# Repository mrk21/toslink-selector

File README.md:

toslink-selector
================

This device is for switching TOSLINK signals automatically.

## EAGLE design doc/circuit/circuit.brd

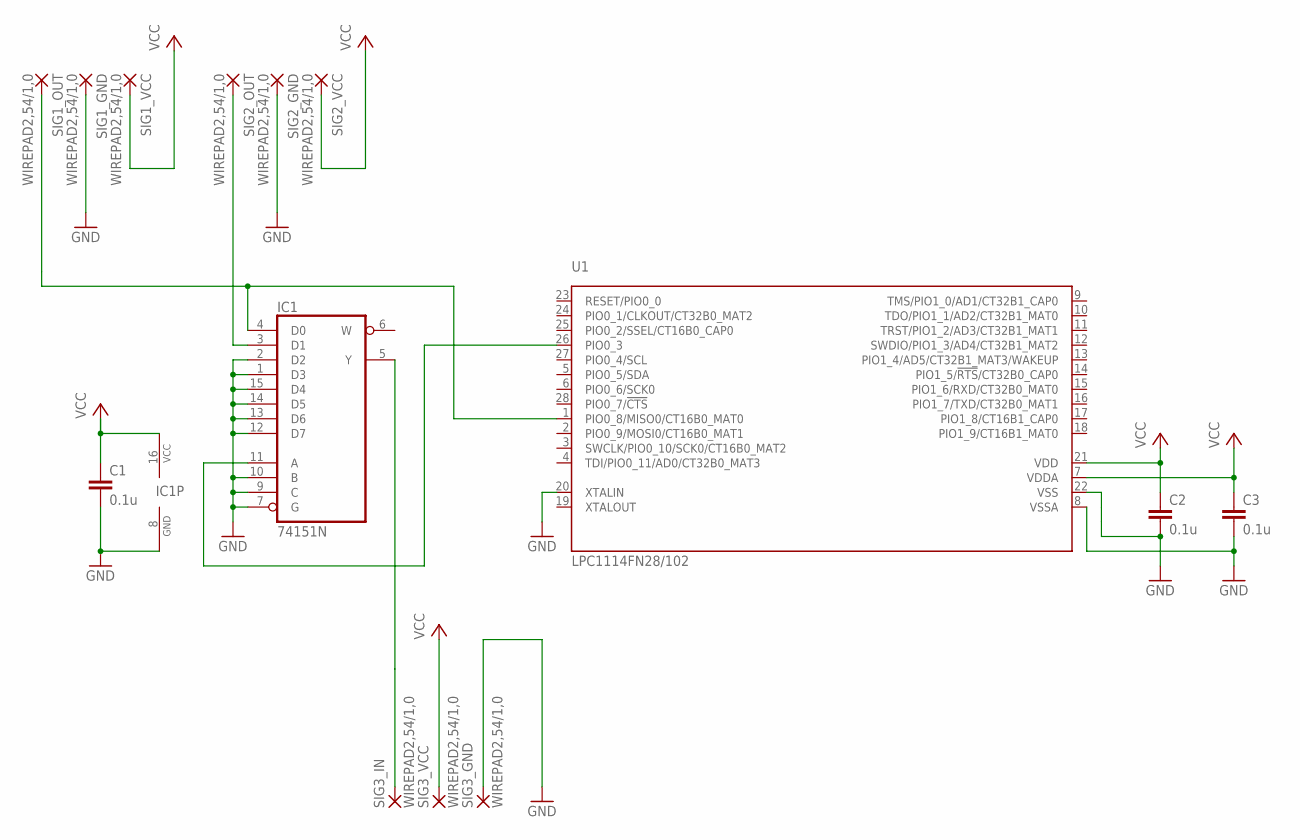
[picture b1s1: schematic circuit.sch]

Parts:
C1, C2, C3: 0.1u; C025-024X044
IC1: 74151N; DIL16
SIG1_GND, SIG1_OUT, SIG1_VCC, SIG2_GND, SIG2_OUT, SIG2_VCC, SIG3_GND, SIG3_IN, SIG3_VCC: WIREPAD2,54/1,0; 2,54/1,0
U1: LPC1114FN28/102; SOT117

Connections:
GND: C1.2, C2.2, C3.2, IC1.1 (D3), IC1.2 (D2), IC1.7 (G), IC1.8 (GND), IC1.9 (C), IC1.10 (B), IC1.12 (D7), IC1.13 (D6), IC1.14 (D5), IC1.15 (D4), SIG1_GND.1, SIG2_GND.1, SIG3_GND.1, U1.8 (VSSA), U1.20 (XTALIN), U1.22 (VSS)
unnamed: IC1.4 (D0), SIG1_OUT.1, U1.1 (PIO0_8/MISO0/CT16B0_MAT0)
unnamed: IC1.11 (A), U1.26 (PIO0_3)
unnamed: IC1.5 (Y), SIG3_IN.1
unnamed: IC1.3 (D1), SIG2_OUT.1
VCC: C1.1, C2.1, C3.1, IC1.16 (VCC), SIG1_VCC.1, SIG2_VCC.1, SIG3_VCC.1, U1.7 (VDDA), U1.21 (VDD)

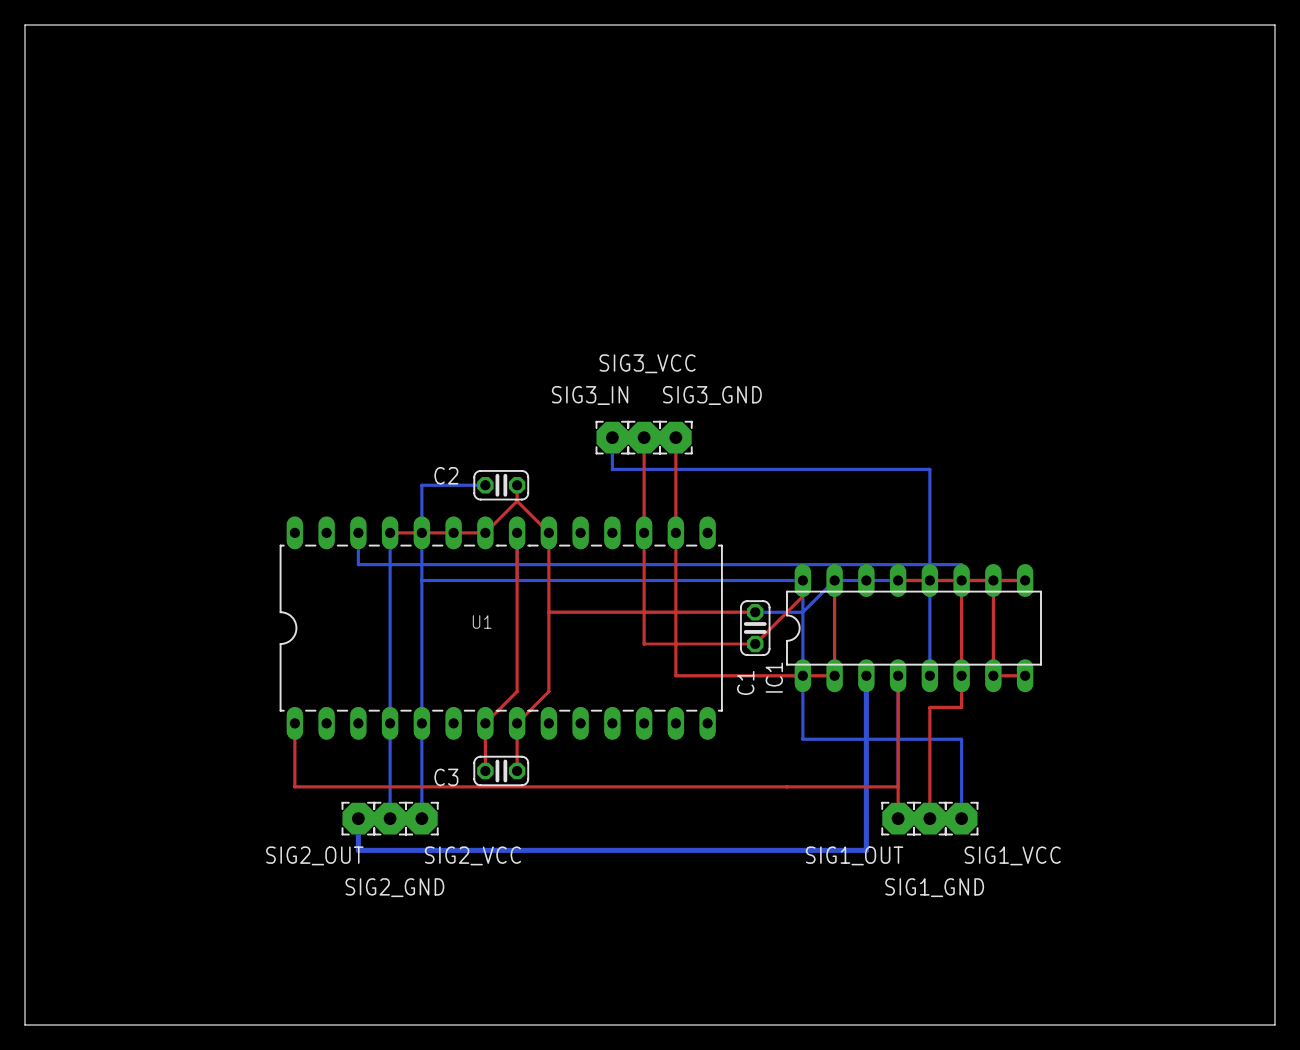
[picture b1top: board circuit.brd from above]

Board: 2 copper layers, 100.0 x 80.0 mm, 14 parts (0 on the bottom side), 6 nets.

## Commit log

2013-10-19 fixes #208.
2013-10-19 fixes #209.
2013-10-25 fixes #221.
2015-03-28 Added captures.
2015-03-28 Create LICENSE
2015-03-28 Updated README.md.
